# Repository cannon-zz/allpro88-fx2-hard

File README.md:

# Cypress FX2 Based Controller for Logical Devices' ALLPRO88 Software-Driven Device Programmer

## Overview

Thanks to the skilled work of kevtris reverse engineering one of these units and his kind generous sharing of his documents (http://blog.kevtris.org/blogfiles/allpro88/), I was able to design and put together this EZ-USB FX2LP based controller to get my own unit going.

You can build your own easily with some pin header socket connectors, a protoboard, three resistors, and one of the "USB logic analyzer" boards you can find on AliExpress.  The "logic analyzer boards", as they're called, are actually just Cypress' FX2LP development board reference design.  The boards get shipped with a logic analyzer firmware which seems to have been ripped off some other product or another, but what's in the EEPROM is irrelevant, it gets replaced with this project's firmware.  Those boards are breakout boards providing access to all of the pins that are needed to implement this circuit.

What's here is the schematic of the circuit to build.  It's also a PCB layout that implements it.  If, instead of using this PCB, you go the route of using a USB logic analyzer board as-is, there is a small difference in the power management that needs to be considered, which will be mentioned below.

For the firmware that goes with this controller, see https://github.com/cannon-zz/allpro88-fx2-soft.

For more information about the ALLPRO88 hardware, including repair tips for the channel driver boards and hybrids, and a kicad template to use as a starting point for custom socket modules, see
- https://github.com/cannon-zz/allpro88-pin-driver
- https://github.com/cannon-zz/allpro88-pin-driver-hybrid
- https://github.com/cannon-zz/allpro88-socket-module

## Circuit Description

### Overview

The FX2LP chip provides an 8051 micro-controller running at a speedy 48 MHz.  The chip includes a USB device interface, which we use to get commands from the host and respond to queries.  It has an I2C master interface used mainly to extract a firmware image at boot from an external EEPROM, but that is available to be used for other stuff if one wishes.  The 56 pin FX2LP version used here also provides 3 8-bit general-purpose I/O ports, and 3 additional I/O pins intended to be used as control lines.

The chip runs at 3.3 V but all of the I/O lines are 5 V tolerant and will tolerate voltages on them even if the chip is off, making interfacing it to legacy 5 V circuitry very simple.

The ALLPRO88's original interface was a 36 pin ribbon cable connecting it to an ISA card.  The 36 lines consist of an 8 bit bi-directional data bus, a 12 bit address bus, three active-low control lines (!READ, !WRITE, and !RESET), and then a whole pile of grounds for signal integrity.  All signals are 5 V TTL logic compatible.

What we do is remove the cable, plug the FX2LP into the ALLPRO88's motherboard where the cable used to be, use two of the 3 control lines to drive the !READ, and !WRITE, lines, one of the 8 bit I/O ports to talk to the data bus, 1.5 of the other two 8 bit I/O ports to talk to the address bus, and finally one of the spare GPIO pins to control the !RESET line.  We route a USB connection to the hole on the ALLPRO88's back panel where the 36 pin connector used to be.  We siphon 5 V from a DIP socket on the ALLPRO88's motherboard, and use a 3.3 V linear regulator to power the FX2LP directly from the ALLPRO88.

### ALLPRO88 Bus Interface

Because of the design of the FX2LP's GPIO scripting system, the data bus must be connected to port B.  The !READ and !WRITE control lines must be connected to the FX2LP's programmable control lines.  Because the !RESET line is never toggled as part of I/O transactions we can connect it to a GPIO port, and use the third programmable control line for a status light that blinks when I/O is occurring.  That leaves the address bus being connected to port A and half of port D.

The FX2LP is 5 V tolerant, so no level shifting circuitry is required.

The ALLPRO88's motherboard has a pair of resistor array chips acting as bus terminators for the 36 conductor interface cable.  They're two orange DIP packages next to the pin header for the cable.  These need to be removed from the motherboard.  At one time I believed they put too great a load on the FX2LP's I/O pins.  I'm not sure about that anymore, but what is definitely true is that (i) they are not needed because there is no bus to terminate, only a few centimetres of PCB traces connect the FX2LP to the chips on the motherboard;  and (ii) they're too close to the pin header onto which the interface board mounts and they interfere with the board if they're left installed.

### Power

5 V and GND are available on the usual pins of those DIP resistor array packages, so after removing them that provides a convenient source of power for the interface board.  I suggest soldering a pair of wires into the appropriate holes and running them to a connector.  Powering the FX2 from the ALLPRO88 and not from the USB bus is necessary because doing so ensures the FX2's firmware runs through the correct hardware reset sequence for the ALLPRO88 when the system is turned on.  Without at least the !RESET line being held in the asserted state, the ALLPRO88 powers up with its control registers set to random values and it can damage itself.

If you choose to build this using a USB logic analyzer board as-is, those boards are powered by the USB bus and some modifications are needed to power them from the ALLPRO88.  In every example I've seen, those boards include a surface-mount fuse in series with a through-hole push-button switch that feed the USB connector's VBUS pin (+5 V) to the input of a 3-pin 3.3 V linear regulator.  Remove the through-hole switch, and that gives you some empty through-holes to which jumper wires can be soldered.  The hole that was the VBUS side of the switch needs to be wired to the WAKEUP pin on the development board's headers through a resistor and capacitor network as in this circuit.  The hole that was the other of the switch, the side connected to the 3.3 V regulator's input, can be where a wire from the ALPPRO88's 5 V supply gets soldered.  If you're lucky, your board's switch will have been mounted on the same 2.54 mm pitch layout grid as the pin headers, and it's holes will be aligned with holes on the protoboard to which you're attaching it, allowing pins and pin sockets to be used to conveniently jumper the holes the switch used to be in to the protoboard and do all this wiring there.

## Assembly

### Parts Source

If you have a hot air soldering station, the cheapest way to build one of these is to order a USB logic analyzer and salvage the parts from it.  Almost all of the required parts can be obtained from one of those boards, they can be had for well under $10 delivered, whereas the FX2LP part, alone, is more than $20 from Mouser (with delivery extra).  Without a hot air station removing the parts without damaging them will be very difficult.  In that case just buy them all new.  (the price difference doesn't come close to justifying buying a hot air station, but if you were thinking of getting one anyway maybe this is the time).

### Soldering Tips

Install the FX2LP first.  Hand-soldering it requires patience, and the more space you have to work the more patient you'll be, so it's best if there's not yet other stuff on the board.  Get a magnifying glass and check each pin of the chip one-by-one to make sure solder has flowed onto it and onto the pad, and hasn't bridged between pins.  Solder flux is your friend.  Everything else is easy to install.

### ALLPRO88 Connection

Two footprints are provided for a female pin header connector for the connection to the ALLPRO88 motherboard.  One option is a TE Connectivity 532956-6.  This is not cheap, but matches the style of the connectors used on the other boards in the system.  An alternative footprint is available for a standard, cheaper, right-angle female header connector as you'd find when doing a search for such things.

### USB Connection

There are two options for the USB connection to the PCB:  a footprint for a USB connector, and a footprint for soldered-in USB cable.  This is not the connection that the cable from the host PC makes, this is for an internal connection within the ALLPRO88 from the interface board to a USB connector on the rear panel (and that's where the cable from the host connects to).  The directly-soldered-cable option is less likely to become a point of failure in the future, but it means the interface board cannot be removed from the chassis without unscrewing the USB connector plate from the rear panel.  That can become inconvenient.  I initially soldered a cable directly to the board, then later decided I preferred having a connector I can pull a cable out of.

For the rear panel, I bought a USB 2.0 type B break-out board.  The shell of a USB 2.0 type B connector is almost exactly the height of the shell of the DB36 connector removed from the rear panel, and fits nicely into the space left by the connector.  I prefer the larger USB connectors, they're more resilient.  We're not sending this stupid thing into space, use a big connector.  To install it in the hole, I bought a piece of 90 degree aluminum angle extrusion at a local hobby shop.  I cut it to a suitable length with a hack saw, and then used a drill, a small file, and lots of patience to carve out holes and notches for the USB connector and its break-out board.  I reused the original screws from the DB36 connector to mount the aluminum angle into the ALLPRO88 case.

Just a little blue paint, and it would look like it was always that way.

### Other Connections

I2C and GPIO headers.  These can be left unpopulated.  It's hard to find connectors that fit into the pin pitch I chose.  That's my bad.  They're not used for anything, they're just there in case somebody wants to play with them in the future.  There are three spare GPIO lines on port D that get routed to J8, along with 3.3 V and GND.  The FX2's I2C clock and data lines, and 3.3 V and GND, are routed to J1.  The ALLPRO88's socket module connectors have many unused pins on them, and one could jumper these signals from the controller board to unused pins on the socket module connectors on the ALLPRO88's motherboard, thereby making them available to custom socket modules.  A little I2C display could be added to show status messages, for example.

## Smoke Test and Firmware Upload

DO NOT connect the module to the ALLPRO88 before writing the proper firmware to the EEPROM.  Apply power to the board and see if it looks OK.  If you don't have a bench power supply for this, find an old 5 V USB wall wart charger and sacrifice it.  Don't try powering the board from the ALLPRO88 because, as mentioned above, the ALLPRO88 needs a hardware reset at start-up otherwise it can damage itself, and for that it needs this controller to be installed.  If the board hasn't caught fire, and the 3.3 V test point shows the correct voltage, plug it into your computer with a USB cable and see what it shows up as.  If you salvaged parts from a USB logic analyzer board, or you are using one of those boards as is, it should show up as that, otherwise it'll probably show up as an FX2 chip in its unprogrammed state.  Either way that tells you it's working.  Write the firmware to the EEPROM, then power cycle the board and it should report itself as an ALLPRO88 USB interface.

NOW you can connect it into the ALLPRO88's motherboard.  With the controller installed, turn on the ALLPRO88.  The "IDLE" light on the socket module should be on, and the "BUSY" light on the socket module should briefly blink.  When the controller is turned on, it enables the main power supply and runs through a channel scan to determine which pin driver modules are installed.  That process is the BUSY light blinking.  If you don't see the light blink once, briefly, or the IDLE light is not on, probably something's wrong.

If, when you apply power, the BUSY light comes on and stays on, turn off the ALLPRO88.  That almost certainly indicates the !RESET line is not being driven properly.  That needs to be diagnosed and fixed before moving on.  When its interface bus is floating, the ALLPRO88 powers up with the main power supplies active.  I don't know why, it doesn't seem wise, it can potentially damage the circuitry, but that's the design.  !RESET must be asserted to clear that state.  The controller circuit has a pull-down resistor on !RESET to ensure it's held in the asserted state until the FX2 firmware has booted and can take control, so if your BUSY light is on and won't turn off it means that the pull-down resistor is not doing what it's supposed to do and also that the FX2 firmware is not starting and doing what it needs to do.  Both are serious problems that need to be rectified.

## Service Suggestions

If you are in the process of getting an ALLPRO88 up and running, whether using this controller to do so or some other trick, here are some hints for things to check before closing it up.

 * Check the heat sinks in the power supplies.  The heatsink for the FET in the VADJ power supply in one of my units was not mounted properly, the bolt missed the hole and the heatsink was just sort of sqeezed there between the transistor and the PCB and was sort of free to wiggle around.  It was sufficiently out of place that it was shorting one of the transistor's pins to a pin on a neighbouring component.  Luckily those two are actually connected in the circuit but who knows what mischief it had gotten up to in the past.

 * The electrolytic capacitors in the power supplies should be replaced.  They predate the age of the capacitor plague, so you won't find a disaster waiting for you, but they're old and doing duty in switching power supplies.  Most of mine had begun to leak stuff onto the PCBs, but nothing serious yet.

 * When replacing them, note that three of the original capacitors are not suitable parts, and need to be replaced with capacitors having different ratings:

   * The UNREG power supply's C7, an electrolytic mounted between the input connector from the transformer and the switching regulator, is an "Elite" brand (?) 470 uF 25 V capacitor.  This capacitor is in parallel with a bunch of other capacitors all rated for 50 V and, yes, this part of the circuit can be expected to see voltages over 25 V ... so ... I don't know what's going on.  The schematic clearly shows that this *is* the capacitor that should be there, and shows that its ratings don't match those of its partners in that circuit.  This capacitor is obviously different from everything else in the power supply, and my guess is that they wanted a lower ESR for this capacitor right next to the regulator and after discussing with the manufacturer decided that they could use this specific capacitor in this off-label application.  Don't try it.  I think any modern, quality, low ESR capacitor will significantly outperform the original part, anyway, so just get a good capacitor rated for the same voltage as the others.

   * There are two electrolytic capacitors providing input and output filtering for an LM79M05CT linear regulator on the ANALOGUE 1 board.  The input capacitor is 2.2 uF and the output capacitor is 1 uF, both rated for 50 V.  If you check the datasheet for that regulator, you'll see that it does recommend those capacities but it specifically says they *must* be tantalums.  If electrolytics are used, the capacitances should be at least 20x higher.  The datasheet suggests 25 uF for the output and nothing less than 50 uF for the input if electrolytics are used.  I guess the engineers missed that remark in the datasheet.  Maybe there's enough capacitance elsewhere in the circuit on this regulator's input and output rails that it doesn't really matter, but I went with what the datasheet says.  I had a 6.8 uF solid tantalum in my parts bin that I used for the input capacitor, and a 1 uF multi-layer ceramic chip on hand that I used for the output.

 * You might observe the 5 V rail supplying all the logic chips in the system to be quite low at the far end of the unit, farthest from the 5 V power supply.  In mine I think I was observing 4.8 V or something on the last channel driver module.  Still in spec for TTL chips, but only just barely.  I recommend replacing the voltage feed-back sense resistors in the 5 V supply to increase its output voltage slightly.  I installed a 1.8 kOhm + 5.6 kOhm pair, both 1% tolerance.  That adds about 0.1 V, it sets the regulator's nominal output to 5.15 V (I measured 5.14 V in mine), and that gives me voltages on the logic chips ranging from 5.1 V closest to the power supply to 4.9 V farthest.

 * If you care, the efficiency of the switching power supplies can be significantly improved, reducing the heat produced in the unit, simply by installing new diodes and transistors.  I damaged the -9 V supply in one of my units, and learned about the improvements when picking out replacement parts.  The -9 V supply, as well as some others, use 1N5822 diodes and RFP12P08 P-channel FETs.  I have found that modern diodes labelled 1N5822 are probably something else, and have *much* lower forward bias voltages than the limit given in the datasheet.  Likewise, a TJ11A10M3 FET can substitute for an RFP12P08 and has only 1/3 the on resistance, dissipating 3x less power in itself than the original transistor.  The latter were available locally but are already obsolete parts, so probably whatever newer thing you can find will be even better.

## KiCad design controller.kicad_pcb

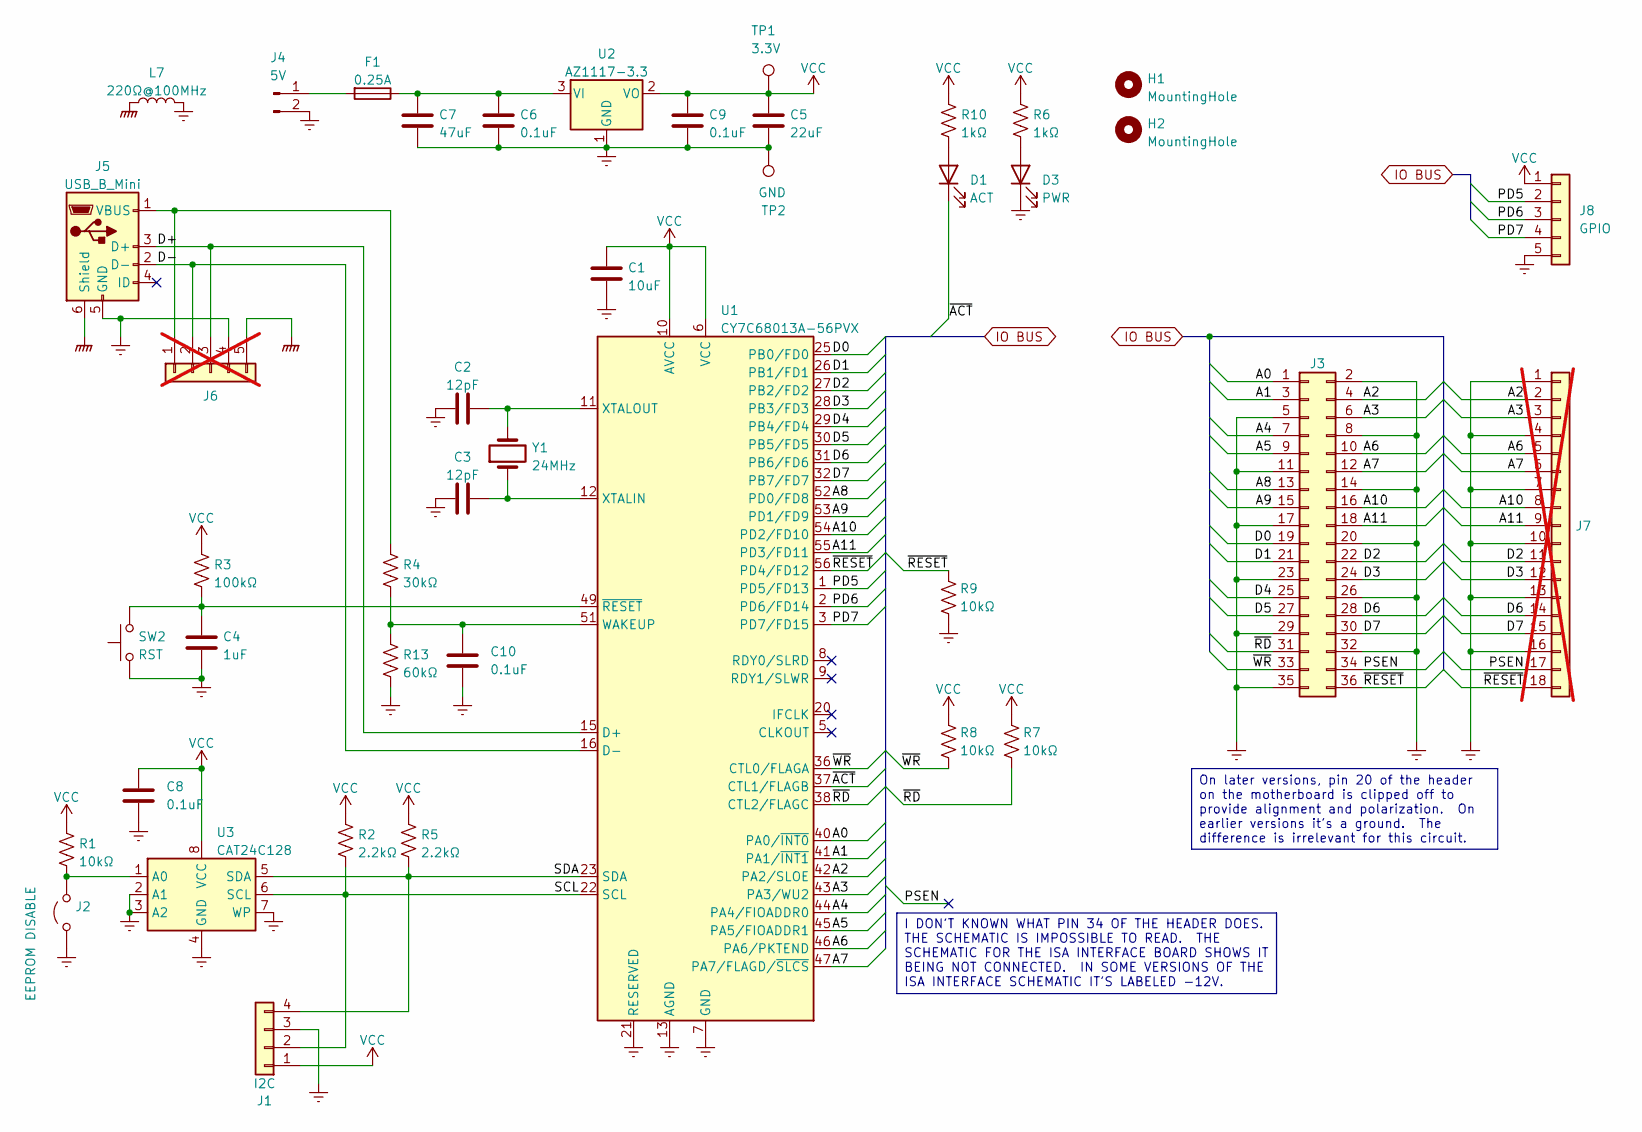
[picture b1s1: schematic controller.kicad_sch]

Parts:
C1: 10uF; C_0805_2012Metric_Pad1.18x1.45mm_HandSolder
C2, C3: 12pF; C_0805_2012Metric_Pad1.18x1.45mm_HandSolder
C4: 1uF; C_0805_2012Metric_Pad1.18x1.45mm_HandSolder
C5: 22uF; C_0805_2012Metric_Pad1.18x1.45mm_HandSolder
C6, C8, C9, C10: 0.1uF; C_0805_2012Metric_Pad1.18x1.45mm_HandSolder
C7: 47uF; C_0805_2012Metric_Pad1.18x1.45mm_HandSolder
D1: ACT; LED_1206_3216Metric_Pad1.42x1.75mm_HandSolder
D3: PWR; LED_1206_3216Metric_Pad1.42x1.75mm_HandSolder
F1: 0.25A; Fuse_1206_3216Metric_Pad1.42x1.75mm_HandSolder
H1, H2: MountingHole; MountingHole_3.2mm_M3
J1: I2C; PinHeader_1x04_P1.27mm_Vertical
J2: EEPROM DISABLE; PinHeader_1x02_P2.54mm_Vertical
J3: Conn_02x18_Odd_Even; PinSocket_2x18_P2.54mm_Horizontal
J4: 5V; TE_440054-2_1x02_P2.00mm_Vertical
J5: USB_B_Mini; USB_Mini-B_Lumberg_2486_01_Horizontal
J6: Conn_01x05; PinHeader_1x05_P1.27mm_Vertical; not fitted
J7: Conn_01x18; PinSocket_1x18_P2.54mm_Vertical; not fitted
J8: GPIO; PinHeader_1x05_P1.27mm_Vertical
L7: 220Ω@100MHz; L_1206_3216Metric_Pad1.42x1.75mm_HandSolder
R1, R7, R8, R9: 10kΩ; R_0805_2012Metric_Pad1.20x1.40mm_HandSolder
R2, R5: 2.2kΩ; R_0805_2012Metric_Pad1.20x1.40mm_HandSolder
R3: 100kΩ; R_0805_2012Metric_Pad1.20x1.40mm_HandSolder
R4: 30kΩ; R_0805_2012Metric_Pad1.20x1.40mm_HandSolder
R6, R10: 1kΩ; R_0805_2012Metric_Pad1.20x1.40mm_HandSolder
R13: 60kΩ; R_0805_2012Metric_Pad1.20x1.40mm_HandSolder
SW2: RST; SW_SPST_FSMSM
TP1: 3.3V; TestPoint_THTPad_1.0x1.0mm_Drill0.5mm
TP2: GND; TestPoint_Loop_D2.50mm_Drill1.0mm
U1: CY7C68013A-56PVX; SSOP-56_7.5x18.5mm_P0.635mm
U2: AZ1117-3.3; SOT-89-3_Handsoldering
U3: CAT24C128; SOIC-8_3.9x4.9mm_P1.27mm
Y1: 24MHz; Crystal_HC49-4H_Vertical

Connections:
/A0: J3.1, U1.40 (PA0/~INT0)
/A1: J3.3, U1.41 (PA1/~INT1)
/A2: J3.4, J7.2, U1.42 (PA2/SLOE)
/A3: J3.6, J7.3, U1.43 (PA3/WU2)
/A4: J3.7, U1.44 (PA4/FIOADDR0)
/A5: J3.9, U1.45 (PA5/FIOADDR1)
/A6: J3.10, J7.5, U1.46 (PA6/PKTEND)
/A7: J3.12, J7.6, U1.47 (PA7/FLAGD/~SLCS)
/A8: J3.13, U1.52 (PD0/FD8)
/A9: J3.15, U1.53 (PD1/FD9)
/A10: J3.16, J7.8, U1.54 (PD2/FD10)
/A11: J3.18, J7.9, U1.55 (PD3/FD11)
/D0: J3.19, U1.25 (PB0/FD0)
/D1: J3.21, U1.26 (PB1/FD1)
/D2: J3.22, J7.11, U1.27 (PB2/FD2)
/D3: J3.24, J7.12, U1.28 (PB3/FD3)
/D4: J3.25, U1.29 (PB4/FD4)
/D5: J3.27, U1.30 (PB5/FD5)
/D6: J3.28, J7.14, U1.31 (PB6/FD6)
/D7: J3.30, J7.15, U1.32 (PB7/FD7)
/D+: J5.3 (D+), J6.3, U1.15 (D+)
/D-: J5.2 (D-), J6.2, U1.16 (D-)
/PD5: J8.2, U1.1 (PD5/FD13)
/PD6: J8.3, U1.2 (PD6/FD14)
/PD7: J8.4, U1.3 (PD7/FD15)
/PSEN: J3.34, J7.17
/SCL: J1.2, R2.2, U1.22 (SCL), U3.6 (SCL)
/SDA: J1.4, R5.2, U1.23 (SDA), U3.5 (SDA)
/~ACT: D1.1 (K), U1.37 (CTL1/FLAGB)
/~RD: J3.31, R7.2, U1.38 (CTL2/FLAGC)
/~RESET: J3.36, J7.18, R9.1, U1.56 (PD4/FD12)
/~WR: J3.33, R8.2, U1.36 (CTL0/FLAGA)
GNDPWR: J5.6 (Shield), J6.5, L7.1
GNDREF: C1.2, C2.1, C3.2, C4.2, C5.2, C6.2, C7.2, C8.2, C9.2, C10.2, D3.1 (K), J1.3, J2.1 (A), J3.2, J3.5, J3.8, J3.11, J3.14, J3.17, J3.20, J3.23, J3.26, J3.29, J3.32, J3.35, J4.2, J5.5 (GND), J6.4, J7.1, J7.4, J7.7, J7.10, J7.13, J7.16, J8.5, L7.2, R9.2, R13.2, SW2.1, TP2.1, U1.4 (GND), U1.7 (GND), U1.13 (AGND), U1.17 (AGND), U1.19 (GND), U1.21 (RESERVED), U1.33 (GND), U1.35 (GND), U1.48 (GND), U2.1 (GND), U3.2 (A1), U3.3 (A2), U3.4 (GND), U3.7 (WP)
unnamed: D1.2 (A), R10.2
unnamed: D3.2 (A), R6.2
unnamed: J2.2 (B), R1.2, U3.1 (A0)
unnamed: F1.2, J4.1
unnamed: J5.1 (VBUS), J6.1, R4.1
unnamed: C10.1, R4.2, R13.1, U1.51 (WAKEUP)
unnamed: C3.1, U1.12 (XTALIN), Y1.1
unnamed: C2.2, U1.11 (XTALOUT), Y1.2
unnamed: C4.1, R3.2, SW2.2, U1.49 (~RESET)
unnamed: C6.1, C7.1, F1.1, U2.3 (VI)
VCC: C1.1, C5.1, C8.1, C9.1, J1.1, J8.1, R1.1, R2.1, R3.1, R5.1, R6.1, R7.1, R8.1, R10.1, TP1.1, U1.6 (VCC), U1.10 (AVCC), U1.14 (AVCC), U1.18 (VCC), U1.24 (VCC), U1.34 (VCC), U1.39 (VCC), U1.50 (VCC), U2.2 (VO), U3.8 (VCC)

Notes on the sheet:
I DON'T KNOWN WHAT PIN 34 OF THE HEADER DOES. THE SCHEMATIC IS IMPOSSIBLE TO READ. THE SCHEMATIC FOR THE ISA INTERFACE BOARD SHOWS IT BEING NOT CONNECTED. IN SOME VERSIONS OF THE ISA INTERFACE SCHEMATIC IT'S LABELED -12V.
On later versions, pin 20 of the header on the motherboard is clipped off to provide alignment and polarization. On earlier versions it's a ground. The difference is irrelevant for this circuit.

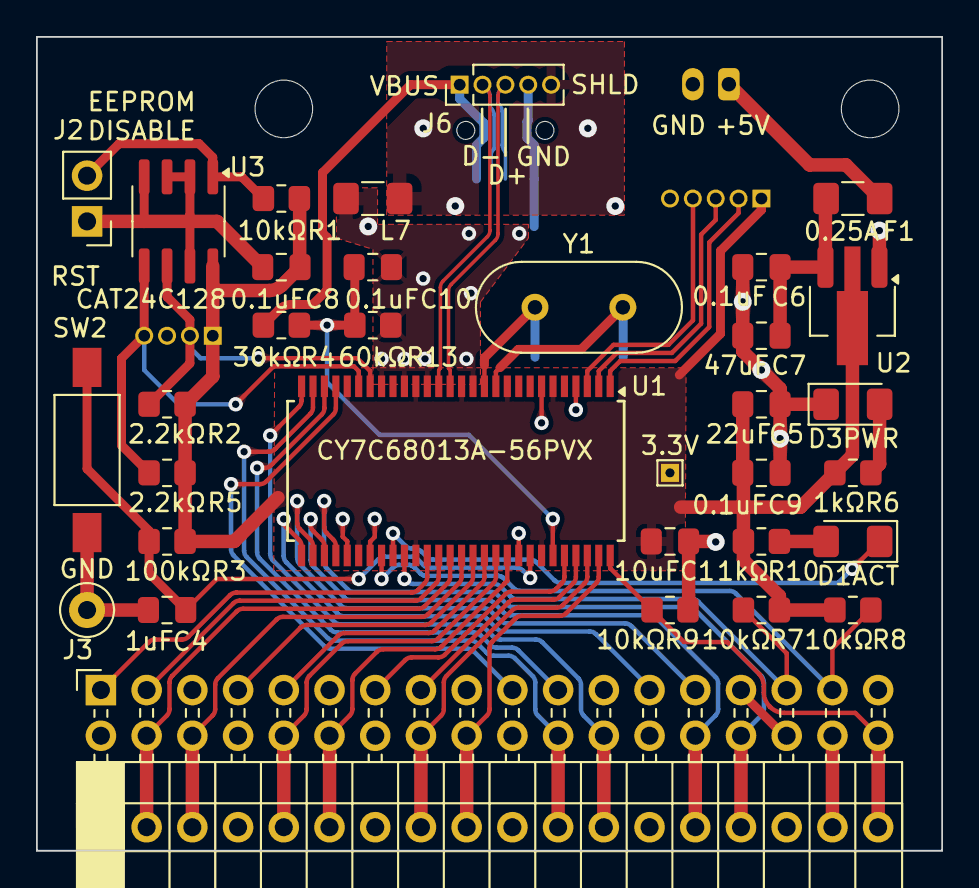
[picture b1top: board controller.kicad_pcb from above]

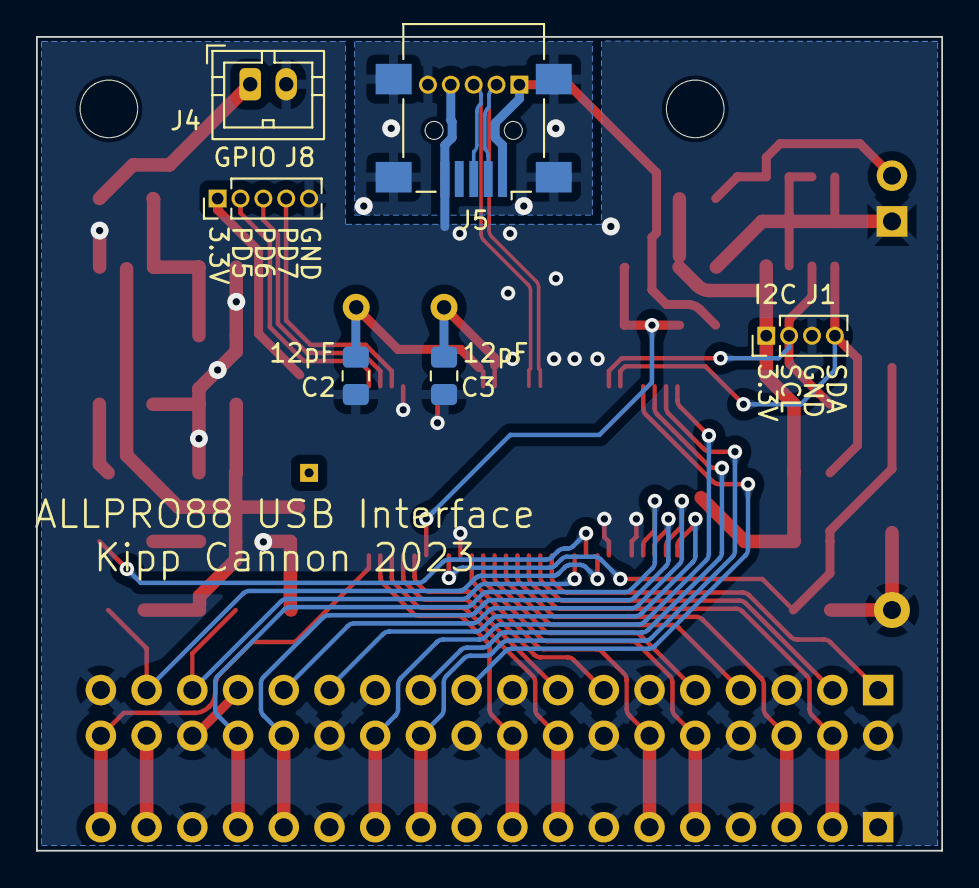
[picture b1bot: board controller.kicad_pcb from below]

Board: 2 copper layers, 50.3 x 45.2 mm, 42 parts (6 on the bottom side), 45 nets.

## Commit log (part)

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2023-07-15 initial commit
    - this is the original schematic with the WAKEUP pin pull-down resistor and timing capacitor added
    - the PCB has had a variety of updates from the original design, but with the exception of the additional resistor and capacitor is the original circuit
    - the changes that might affect reliability:
    - USB D+/D- pair has been routed differently. there are fewer irregularities in their route, but I still have not read the USB design requirements for this differential pair. I know the original boar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
    - the +ve supply rail for the FX2 chip is now a copper fill area to reduce the impedance between the
2023-07-19 let's call this "version 2"
    - this is a cleaned-up version of the board that was built and installed in the programmer
    - the WAKEUP drain resistor & timing capacitor are included
    - the board is hard-wired into the self-powered configuration (USB VBUS only used for WAKEUP)
    - power delivery to the FX2 chip is (probably) improved
    - the ground plane has fewer interruptions
    - (almost) all spare pads and through-holes to accommodate possible mistakes are removed because they're known to not be needed
2025-01-06 minor improvements
    - update to current symbols and footprints
    - flip the GPIO and I2C pin headers to the back to avoid damage when the case is opened. this just changes the silk screen, one can choose to solder them in either way regardless.
    - kicad now offers a better crystal footprint. switch to it so the holes are more appropriately sized
2025-01-21 open and close with latest version
2025-01-21 remove notes.txt
2025-01-26 add README.md
2025-01-26 edit README.md
2025-01-26 add photos
2025-10-21 don't think I changed anything, just updated kicad
2025-10-21 README.md: edit a bit
    - change the instructions for hacking power on the logic analyzer board. I think it's not optional, you have to power this thing from the ALLPRO88. removing the power switch from one of those things 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
2025-10-21 add GPLv3 license
2025-11-27 add service notes
2025-11-28 README.md
    - found link to kevtris' documents
    - fix a typo
2025-11-29 README.md: less verbosity
